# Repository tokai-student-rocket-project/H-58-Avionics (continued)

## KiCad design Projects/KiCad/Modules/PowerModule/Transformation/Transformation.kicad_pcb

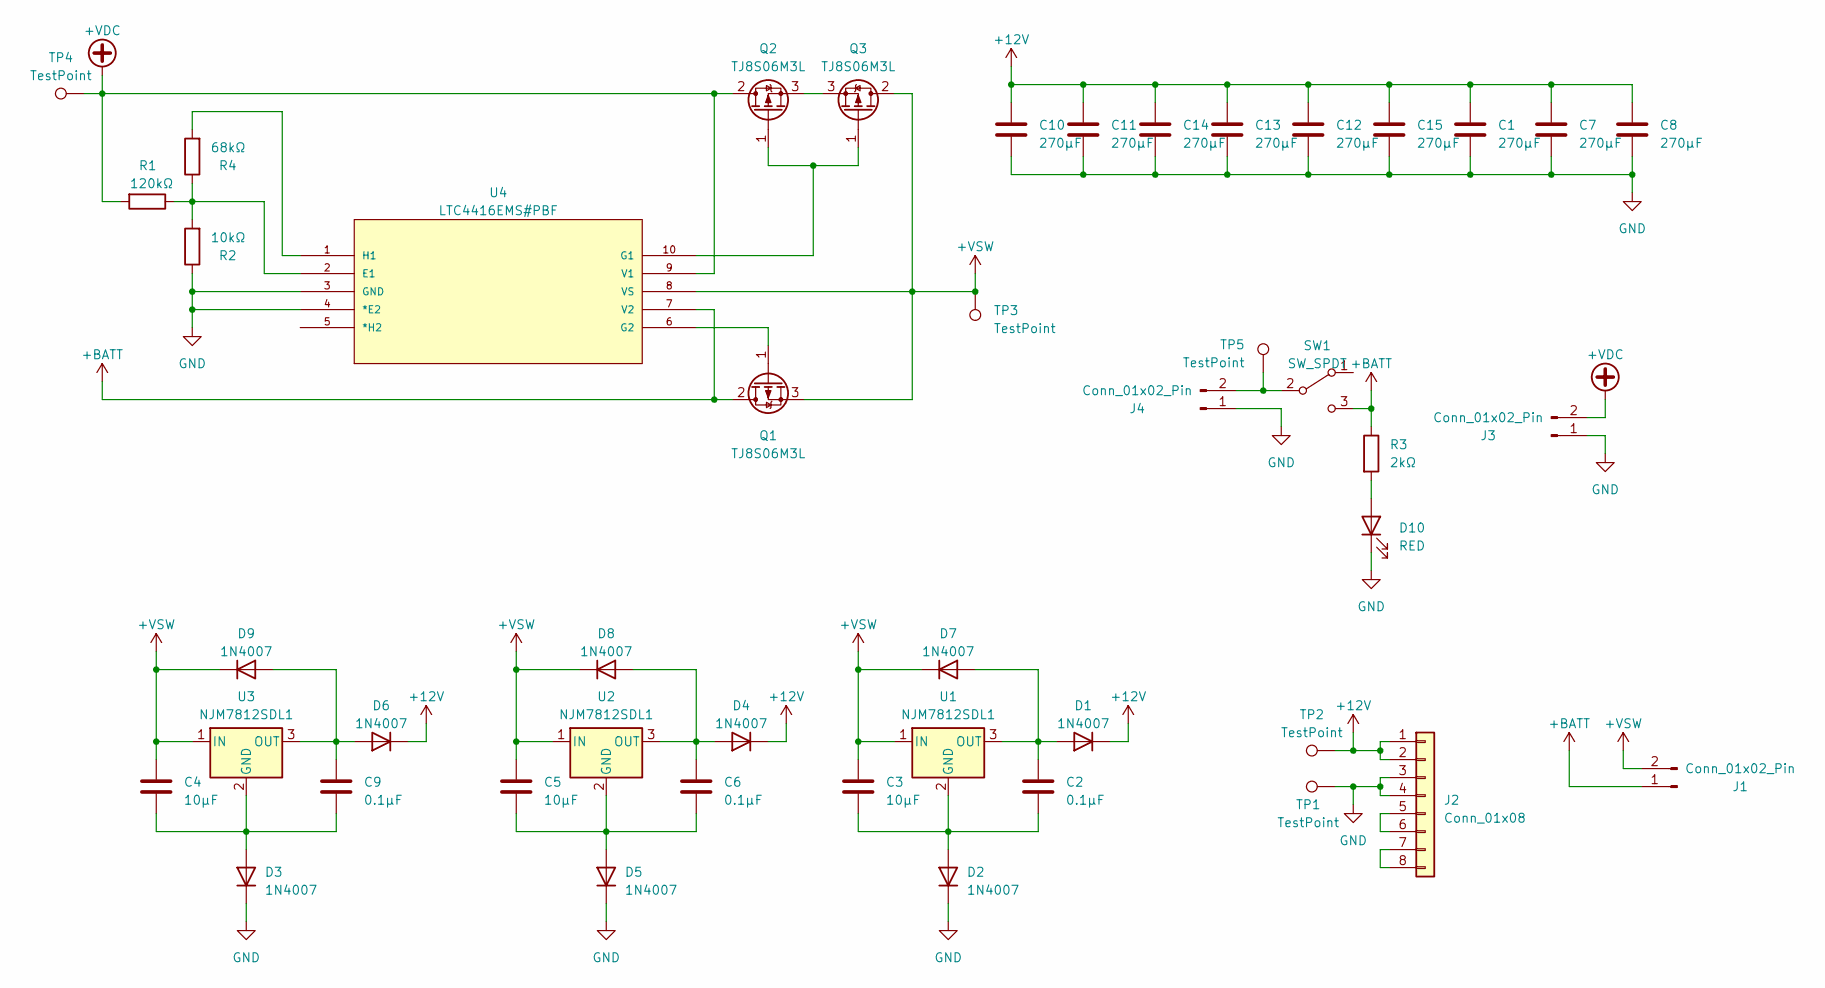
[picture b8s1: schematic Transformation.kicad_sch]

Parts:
C1, C7, C8, C10, C11, C12, C13, C14, C15: 270μF; CP_Radial_D10.0mm_P3.50mm
C2, C6, C9: 0.1μF; C_0603_1608Metric_Pad1.08x0.95mm_HandSolder
C3, C4, C5: 10μF; C_0603_1608Metric_Pad1.08x0.95mm_HandSolder
D1, D2, D3, D4, D5, D6, D7, D8, D9: 1N4007; D_SOD-123F
D10: RED; LED_0603_1608Metric_Pad1.05x0.95mm_HandSolder
J1, J3, J4: Conn_01x02_Pin; Hirose_DF1B
J2: Conn_01x08; Hirose_DF11B-8DP-2DS
Q1, Q2, Q3: TJ8S06M3L; TO-252-2
R1: 120kΩ; R_0805_2012Metric_Pad1.20x1.40mm_HandSolder
R2: 10kΩ; R_0805_2012Metric_Pad1.20x1.40mm_HandSolder
R3: 2kΩ; R_0603_1608Metric_Pad0.98x0.95mm_HandSolder
R4: 68kΩ; R_0603_1608Metric_Pad0.98x0.95mm_HandSolder
SW1: SW_SPDT; 2MS1T1B4M7QES
TP1, TP2, TP3, TP4, TP5: TestPoint; Pin_D1.0mm_L10.0mm
U1, U2, U3: NJM7812SDL1; TO-252-2
U4: LTC4416EMS#PBF; MSOP-10-1EP_3x3mm_P0.5mm_EP1.73x1.98mm; MANUFACTURER_PART_NUMBER ltc4416ims1

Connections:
+12V: C1.1, C7.1, C8.1, C10.1, C11.1, C12.1, C13.1, C14.1, C15.1, D1.1 (K), D4.1 (K), D6.1 (K), J2.1, J2.2, TP2.1
+BATT: J1.1, Q1.2 (D), R3.1, SW1.3 (C), U4.7 (V2)
+VDC: J3.2, Q2.2 (D), R1.2, TP4.1, U4.9 (V1)
+VSW: C3.1, C4.1, C5.1, D7.1 (K), D8.1 (K), D9.1 (K), J1.2, Q1.3 (S), Q3.2 (D), TP3.1, U1.1 (IN), U2.1 (IN), U3.1 (IN), U4.8 (VS)
GND: C1.2, C7.2, C8.2, C10.2, C11.2, C12.2, C13.2, C14.2, C15.2, D2.1 (K), D3.1 (K), D5.1 (K), D10.1 (K), J2.3, J2.4, J3.1, J4.1, R2.1, TP1.1, U4.3 (GND), U4.4 (*E2)
unnamed: C2.1, D1.2 (A), D7.2 (A), U1.3 (OUT)
unnamed: C2.2, C3.2, D2.2 (A), U1.2 (GND)
unnamed: C4.2, C9.2, D3.2 (A), U3.2 (GND)
unnamed: C6.1, D4.2 (A), D8.2 (A), U2.3 (OUT)
unnamed: C5.2, C6.2, D5.2 (A), U2.2 (GND)
unnamed: C9.1, D6.2 (A), D9.2 (A), U3.3 (OUT)
unnamed: D10.2 (A), R3.2
unnamed: J2.5, J2.6
unnamed: J2.7, J2.8
unnamed: J4.2, SW1.2 (B), TP5.1
unnamed: Q1.1 (G), U4.6 (G2)
unnamed: Q2.1 (G), Q3.1 (G), U4.10 (G1)
unnamed: Q2.3 (S), Q3.3 (S)
unnamed: R1.1, R2.2, R4.1, U4.2 (E1)
unnamed: R4.2, U4.1 (H1)

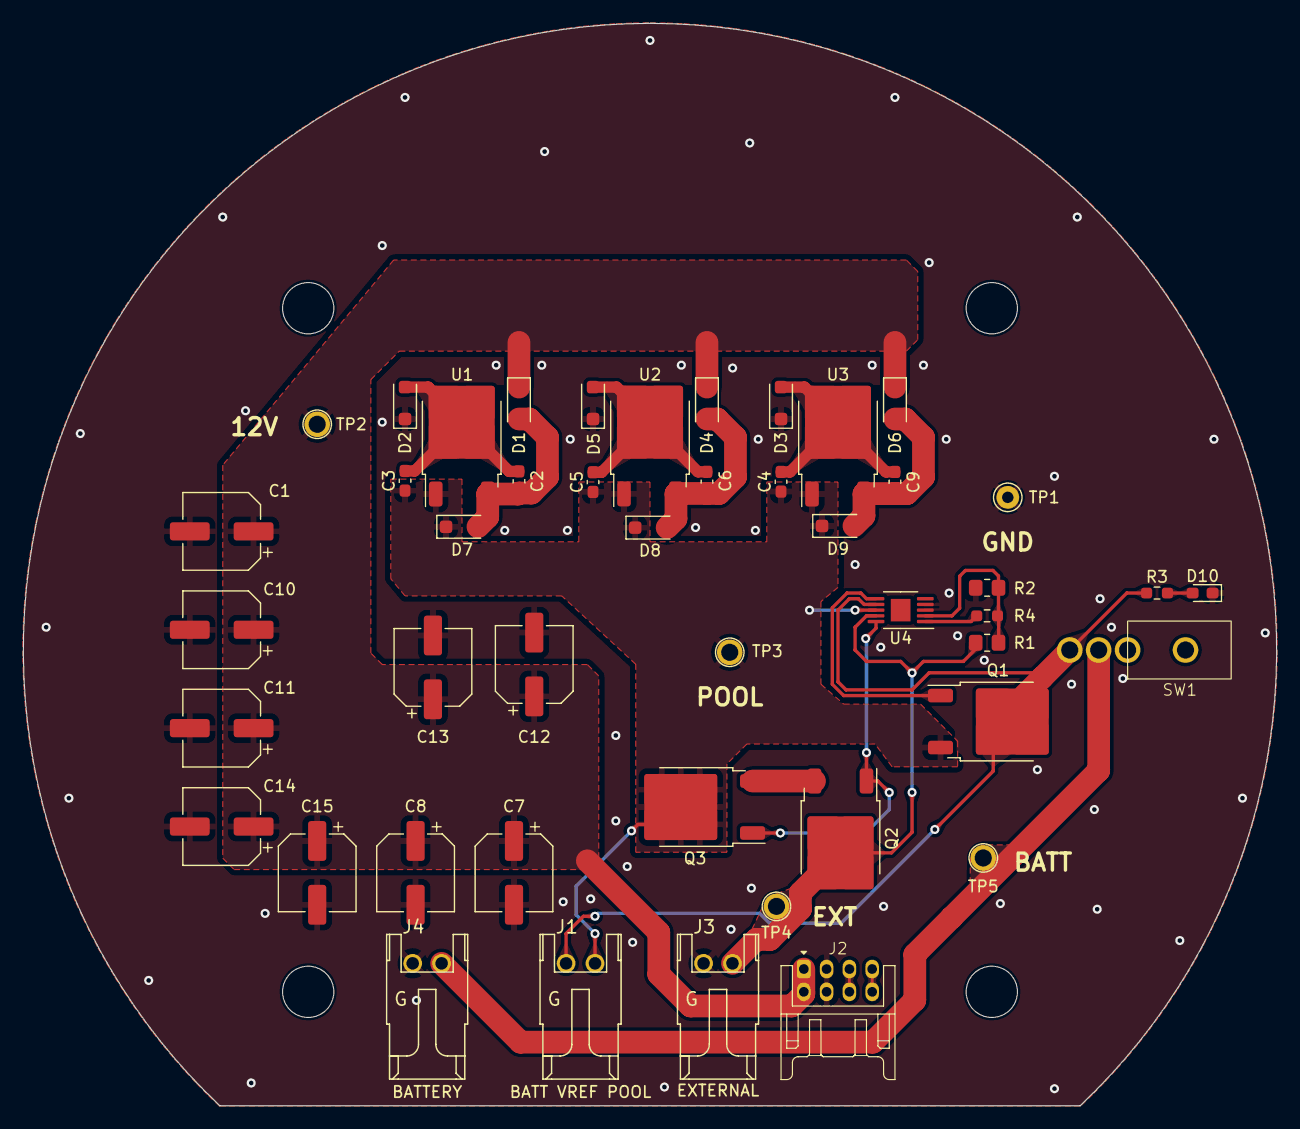
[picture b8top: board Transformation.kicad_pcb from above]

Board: 2 copper layers, 110.0 x 95.0 mm, 46 parts (0 on the bottom side), 20 nets.

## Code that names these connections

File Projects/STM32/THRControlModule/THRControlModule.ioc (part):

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Mcu.Name=STM32F303K(6-8)Tx
Mcu.Package=LQFP32
Mcu.UserName=STM32F303K8Tx
PA10.Mode=Synchronous
PA10.Signal=USART1_RX
PA11.Mode=CAN_Activate
PA11.Signal=CAN_RX
PA12.Mode=CAN_Activate
PA12.Signal=CAN_TX
PA5.Mode=Full_Duplex_Master
PA5.Signal=SPI1_SCK
PA6.Mode=Full_Duplex_Master
PA6.Signal=SPI1_MISO
PA7.Mode=Full_Duplex_Master
PA7.Signal=SPI1_MOSI
PA8.Mode=Synchronous
PA8.Signal=USART1_CK
PA9.Mode=Synchronous
PA9.Signal=USART1_TX
PB0.GPIOParameters=PinState,GPIO_Label
PB0.GPIO_Label=Thermocouple_CS
PB0.PinState=GPIO_PIN_SET
PB0.Signal=GPIO_Output
PF0\ /\ OSC_IN.Mode=HSE-External-Oscillator
PF0\ /\ OSC_IN.Signal=RCC_OSC_IN
PF1\ /\ OSC_OUT.Mode=HSE-External-Oscillator
PF1\ /\ OSC_OUT.Signal=RCC_OSC_OUT
RCC.HSEPLLFreq_Value=8000000
RCC.HSE_VALUE=8000000
RCC.SYSCLKFreq_VALUE=8000000
board=custom

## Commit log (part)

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2023-06-20 Kicadの更新
2023-06-20 CDRおわ
2023-06-20 チャタリング対策を追加
2023-06-21 計測モジュールにCANのラッパライブラリを追加（includeに相対パス指定できないの悲しい）
2023-06-21 フライトモジュールにCANのラッパライブラリを追加
2023-06-21 Arduino向けのCANのラッパライブラリを追加
2023-06-21 ピン初期化周りを変更、100Hzでタスクを回すように変更
2023-06-21 CANの抽象度を上げた
2023-06-21 GSEからバルブ開 バルブ閉を受け取ることができた。
2023-06-21 名前空間を整理
2023-06-21 起動モードがデバッグの時は電圧監視をしないように変更（ピンが競合するため）
2023-06-21 各部名称を変更
2023-06-21 変更後のpngを追加
2023-06-21 不知火の抽象化ライブラリを追加
2023-06-21 SDが不正の時のLED点滅をいい感じのライブラリに移植
2023-06-22 ガーバーを再出力
2023-06-22 バルブ制御モジュールを追加
2023-06-22 基板を更新（最終確認中）
2023-06-22 温度補正を追加中
2023-06-22 リフトオフ検知とリセット検知に連続検知を追加
2023-06-23 BMEのログをとった
2023-06-23 周波数解析を追加
2023-06-23 CANのIdを整理
2023-06-23 CANでやり取りするデータを整理
2023-06-23 フライトモードの遷移と遷移後の動作を統合
2023-06-24 pluginを追加
2023-06-24 ValveControlModuleのガーバーデータを追加
2023-06-24 AdafruitのMAX31855ライブラリーに変更
2023-06-24 Adafruitのライブラリ仕様に変更
2023-06-26 イベントの出力を追加
2023-06-26 CANのイベントのパケット構成を変更
2023-06-26 すべてのモジュールがSETUPイベントを出力するように変更
2023-06-26 unionからmemcpyを使った実装に変更
2023-06-26 CANMCPに送信用の関数を追加
2023-06-26 🚧 ブランチを追加
2023-06-26 🍻 エクセルをゴニョゴニョ変更
2023-06-26 ✨ 強制分離を追加
2023-06-26 🐛 memcpyのポインタを、ミスっていたので修正
2023-06-27 🎨 離昇してからの経過時間を返すflightTime()関数を追加
2023-06-27 EMA計算用のクラスを追加
2023-06-27 頂点検知(!=頂点予測)用のクラスを追加
2023-06-27 ✨ 分離保護を実装
2023-06-27 🎨 無駄にスネークケースだったことろをキャメルケースに修正
2023-06-27 🎨 受信側を更新
2023-06-28 🚚 通信モジュールの受信側のパスを変更
2023-06-28 ✨ ミッションモジュールの受信を追加
2023-06-28 🐛 計測モジュールの気温送信を消していたので追加
2023-06-28 ⚡️ CANの安定化のためにボーレートを80kbpsに変更
2023-06-28 CANのボーレートとTransmitPriorityを変更
2023-06-28 🎨 状態検知を10Hzに変更
2023-06-28 ✨ イベントのダウンリンクを実装
2023-06-28 🎨 フライトピンの状態検知は100Hzに戻した
2023-06-28 🎨 CANのボーレートを変更
2023-06-28 CAN受信LEDの点滅タイミングを欲しいパケットを受信した時のみに修正
2023-07-01 夢の国の音楽を追加
2023-07-01 短音1回, 2回, 長音1回をノンブロックングで追加
2023-07-01 CANのイベントパケットからペイロードデータを削除
2023-07-01 CAN-BUSのリストを更新
2023-07-01 CANのコマンドパケットにはパスワードいらなかったので削除
2023-07-01 参照気圧設定コマンドを追加
2023-07-01 ⚡️ 温度計測の方法を変更
2023-07-03 🚧 ⚡️ ブザータイミングの作業中/ブザーの機能を追加、確認用LEDの追加
2023-07-03 ✨ シャットダウン時に例の曲を流すように変更
2023-07-03 コードをコメントに追加
2023-07-03 🔥 余計なコメントを削除
2023-07-03 💬 コマンド部分のCANリストを変更
2023-07-03 🎨 参照気圧セットコマンドを分割
2023-07-03 🐛 CAN受信処理のラベルを修正
2023-07-03 システムデータ通信モジュールの受信側から計測モジュールへのアップリンクを追加
2023-07-03 ⚡️ 各モード遷移時にブザー音を追加
2023-07-03 ♻️ CANのbpsを変更
2023-07-03 ✏️ 指摘されたので直しました。文句ありますか？
2023-07-03 ✨ 参照気圧を設定できた時にイベントをダウンリンクするように変更
2023-07-03 💬 READMEの参照気圧設定コマンドのデータ長をミスっていたので修正
2023-07-03 💬 READMEのCANリストにエラー追加
2023-07-03 🎉 バルブ制御モジュールにTHR制御モジュール（存在しない）のコードを移植
2023-07-04 🎉 バルブ制御モジュールのコードを追加
2023-07-04 テスト用に製作したフォルダ達を削除
2023-07-04 ✨ キー照合の失敗時のエラーダウンリンクを実装
2023-07-04 伝送試験用に受信側のログ出力を編集
2023-07-04 🎨 ADXLをSPIに変更（通信は未実装）
2023-07-04 ✨ サーボモーターのRAMにアクセスできるようになり、各種パラメータを取得可能に。
2023-07-05 🚧 ADXLの初期化処理をSPIに変更
2023-07-05 🔊 受信側のログ出力をcsvに変更
2023-07-05 ♻️ 余計な個所を微修正
2023-07-05 ログ置き場を作成
2023-07-05 エアーデータコミュニケーションツールを追加
2023-07-05 システムデータコミュニケーションモジュールを追加しました。
2023-07-05 エアーデータコミュニケーションモジュールを追加
2023-07-05 システムモードコミュニケーションモジュールの解析を追加しました。
2023-07-05 練習しました
2023-07-05 ADXLのデータ出力をSPIに変更（出力されない）
2023-07-05 ⏪ 受信側のログをJsonに戻した
2023-07-05 解析のエクセルを追加
2023-07-05 表を整形
2023-07-06 📝 ロングラン試験のREADMEを追加
2023-07-06 ✨ ロングラン用に必要なログをダウンリンクするコードを追加
2023-07-06 ♻️ コードにコメントを追加
2023-07-06 💬 試験の概要的なものをREADMEに記載
2023-07-06 🔊 1回目のロングラン試験のログを追加
2023-07-06 🔊 ログのファイル名を変更
2023-07-06 🔊 2回目のロングラン試験のログを追加
2023-07-06 🔊 速報用の解析を追加
2023-07-06 🔊 ミッションモジュールのログを追加
2023-07-06 🙈 エクセルの一時ファイルをgitignoreに追加
2023-07-06 📝 ミッションモジュールの解析を追加
2023-07-06 🔊 ログを移動
2023-07-06 🔊 1回目のログを整形
2023-07-06 🚚 ログのファイル名を変更
2023-07-06 🔊 2回目のログを整形
2023-07-06 🔊 解析を追加
2023-07-07 ✨ climbIndexの算出を計測モジュールで行うように変更
2023-07-07 ✨ フライトモードの頂点検知を計測モジュールが算出した落下検知を使用したものに変更
2023-07-07 🎨 高度算出をTrajectoryライブラリに移植
2023-07-07 ⚡️ Trajectoryライブラリのupdate()ですでに用意した高度を使用できるように変更
2023-07-07 ⚡️ 読み出すことのできるデータのみ実装
2023-07-07 ✨ CANで送るデータの追加
2023-07-07 ⚡️ CANの動作が行えているかのチェックする機能を追加．言語よわよわなのでコメントアウトで実装
2023-07-07 🎨 読み出す値のコメントを追加．
2023-07-07 頂点検知試験用のコードを追加
2023-07-08 レジスタの書き込みをwrite()関数に切り出し
2023-07-08 🧐 Adafruitライブラリでは動作することを確認
2023-07-08 ADXLの自作ライブラリでの動作を確認
2023-07-08 🎨 ODRを3200Hzに変更, 出力値の単位をm/s2に変更
2023-07-08 ♻️ SPI関係の関数を整理
2023-07-08 ✨ FRAMの読み書きを実装
2023-07-08 ⚗️ FRAMの容量把握ようの実験コードを追加
2023-07-08 ✨ 簡易的なFRAMへのログ保存を実装
2023-07-08 ✨ フライトモードがSTANDBYとLANDの間のみログを保存するように変更
2023-07-08 🐛 ログ保存OFFの状態で起動するように修正
2023-07-08 ♻️ CAN受信処理を関数に摘出
2023-07-08 ♻️ RecorderからLoggerに名称変更
2023-07-08 💡 inoに一通りコメントを追加
2023-07-08 ♻️ 充填確認との区別のためにTemperatureをOutsideTemperatureに名所変更
2023-07-08 inoの変数に単位を追加
2023-07-08 💡 BMEにコメントを追加
2023-07-08 🚧 コメントを書くコードにTODOを追加
2023-07-10 💡 BNO055にコメントを追加
2023-07-10 計測モジュール関係に一通りコメントを追加
2023-07-10 ♻️ CANの関数receiveStatus()をreceiveSystemStatus()に名称変更
2023-07-10 ♻️ CANの関数からCommandを削除して名称変更
2023-07-10 ♻️ sendVector()をsendVector3Dに名称変更
2023-07-10 ♻️ sendSystemStatus()の引数名をxxStateに変更
2023-07-10 🚧 バッテリー切れ(死)
2023-07-10 Revert "🚧 バッテリー切れ(死)"
    This reverts commit 6ca955eedc5a3f155d30bc1fa7058b48da335df3.
2023-07-10 🔊 H-49とH-57のログを追加
2023-07-10 高度50m以上でないと落下判定しないように変更
2023-07-10 ✏️ 変数名の誤字を修正
2023-07-10 ⚡️ 重そうなSDの認識処理を1Hzタスクに変更
2023-07-10 ⚡️ SDの初期検知を廃止
2023-07-10 🚧 BMEとBNOをコメントアウト
2023-07-10 ⚡️ BNO055ライブラリを最低限の実装で自作
2023-07-10 ⏪ BME280はそのままで
2023-07-10 🎨 LoggerにSdを統合
2023-07-10 ⚡️ SD検知不可時の処理をシンプルに変更
2023-07-10 🔥 不要なコードを削除
2023-07-10 ✨ SDのログ開始を追加
2023-07-10 ✨ ログ保存開始時csvにヘッダーを書き込むように変更」
2023-07-10 ✨ SDへのデータ書き込みを実装(1668Bオーバー)
2023-07-10 ログファイルはMessagePackで保存するようにした
2023-07-10 🎨 SDカードにバイナリで書き込むように変更
2023-07-10 ✨ 毎回新しいファイルを作るように変更
2023-07-10 ✨ SD不正時にエラーを発行するように変更
2023-07-10 ✨ 参照気圧を5秒間隔で送信する機能を追加
2023-07-10 ✨ センサのキャリブレーション状態を送信する機能を追加
2023-07-11 分離制御のロジック図を更新
2023-07-11 頂点検知試験用のモックデータを20Hzに修正
2023-07-11 ✨ SCMでSD不正のエラーを受け取る処理を追加
2023-07-11 ✨ SCMの受信側を実装
2023-07-11 ✨ FRAM動確
2023-07-11 🎨 DoLoggingをCANで送るように変更
2023-07-11 ✨ フライトモジュールにFRAMへのデータ保存を実装
2023-07-12 🐛 FRAMをクリアする前に書き込み位置をリセットするように修正
2023-07-12 🐛 FRAMの容量を超えていてもSDへは書き込むように修正
2023-07-12 🐛 FRAMのクリアの前にライトイネーブルが設定されていなかった問題を修正
2023-07-12 ✨ フライトモジュールのFRAMへのログ保存を実装
2023-07-12 🎨 ログ保存の開始と終了を関数に切り出し
2023-07-12 ✨ 想定着地時間の3秒前にカメラオフにする
2023-07-12 🍻 燃焼中は1kHz計測を行い、後からダウンリンク送信する処理を簡易的に実装
2023-07-12 ♻️ フライトモード変更を関数に切り出し
2023-07-12 💡 コメントを追加
2023-07-12 💡 AnalogVoltageにコメントを追加
2023-07-12 💡 Buzzerにコメントを追加
2023-07-12 🐛 ブザーをトグルする前にOFFにするように修正(一生なり続ける問題解消)
2023-07-12 🎨 ログ保存の状態をLoggerクラス内で保存するように変更
2023-07-12 ✨ フライトモード管理用のライブラリを実装
2023-07-13 ✨ フライトモードを認識する関数を実装
2023-07-13 ✨ フライトモードの初期値をインスタンス化時点でSLEEPにするように変更
2023-07-13 🎨 フライトモードを列挙型の状態で渡すように変更
2023-07-13 💥 列挙型を摘出
2023-07-13 logicを追加
2023-07-13 ✨ CAN通信部を実装
2023-07-13 🎨 OutputPinとPullupPinをもう一段階ラップするクラスを実装
2023-07-13 🐛 SDが不正でもログ開始はするように修正
2023-07-13 SwitchのOPENとCLOSEが逆だったので修正
2023-07-13 ⚡️ パフォーマンス改善のためログ保存開始時にSDが認識できない時は初期化しないように修正
2023-07-13 ⚰️ 不要なインクルードを削除
2023-07-13 🎨 名前空間を整理
2023-07-13 ♻️ 起動モードのスイッチを整理
2023-07-13 🎨 フライトモード遷移時処理の実行手順を変更
2023-07-13 🔀 競合を解消
2023-07-13 🐛 Varを使った実装に修正
2023-07-13 🎨 デバッグ用のコードをコメントアウト
2023-07-13 🐛 CAN受信を修正
2023-07-13 🎨 時間を管理するクラスを実装
2023-07-13 🚧 LoRa管理用のクラスを追加
2023-07-13 🎨 エアデータ通信モジュールでTransmitterを利用するように変更
2023-07-14 ♻️ 不要なコメントアウトを削除
2023-07-14 ✨ バルブ制御モジュールからのCAN受信とダウンリンクを追加
2023-07-14 ✨ Transmitterを簡易的に実装
2023-07-14 ✨ フライトモードオンコマンドを実装
2023-07-14 🔥 Transmitterにメリットを感じなかったので廃止
2023-07-14 ⚡️ CANで送るデータサイズを縮小
2023-07-14 ✨ 現在のモードを10HzでCANに流す機能を追加
2023-07-14 🐛 Taskの名前変更し間違えたので変更
2023-07-14 🚧 エラー送信がうまく動作しているのか確認．
2023-07-14 ✨ バルブ制御モジュールのLAUNCH信号状態検知でフライトモードを開始を実装
2023-07-14 🚧 PC移動コミット
2023-07-15 🔥 バルブ制御モードの連続検知を廃止
2023-07-17 💡 自作ライブラリたちにコメントを追加
2023-07-17 💡 通信モジュールにコメントを追加
2023-07-19 ⚡️ CAN送信レートを変更
2023-07-19 ⚡️ 送信レートを素数に変更
2023-07-19 ⚡️ 燃焼実験時のコンフィグを確定
2023-07-20 フライトピンの接触不良でした
2023-07-22 🐛 ダウンリンクを調整
2023-07-22 🐛 姿勢角と偽って地磁気を送信していた問題を修正
2023-07-25 📝 手順書用の写真を追加
2023-07-25 ✨ 上昇率の算出を実装
2023-07-25 ⚡️ エアデータを平滑化するように変更
2023-07-25 電圧3種類を1つのパケットに圧縮
2023-07-25 🐛 電圧をCAN送信の引数が間違っていたので修正
2023-07-26 飛翔時間のダウンリンクを追加
2023-07-26 🏷️ ステータスをダウンリンクするときの型をuint8_tからboolに変更
2023-07-26 ⚡️ コマンドの受信成功率を改善
2023-07-26 🐛 座標軸を修正
2023-07-28 広報に関する情報を追加
2023-07-28 ペーパークラフトを追加
2023-07-28 noteとasideの試し
2023-07-28 noteとasideは使えなかった
2023-07-28 note infoも無理
2023-07-29 ✨ 計測モジュールにダンパーを追加
2023-07-29 ✨ ダンパーを追加
2023-07-29 ⚡️ mcu温度とmotor温度を温度系としてまとめた（はず...） 大学行く前コミット
2023-07-29 LEDをオフ
2023-07-29 ⚡️ motor温度，mcu温度，電流，電圧を１つにまとめた
2023-07-29 3023948a56a2dfa1adf925e6bd497c5dc962d727 これに対応
2023-07-29 LoRaの送信キューを実装
2023-07-29 ⚡️ モーターに関するデータを1つに集約してCANへ送る機能の追加
2023-07-29 ✨ バルブ角度の受信を追加
2023-07-30 くぁｓｗでｆｒｔｇｙふじこｌｐ
2023-07-30 🔥 処理をまとめたので余計な処理を削除
2023-07-30 🔥 ValveControlModuleに主な機能を譲渡
2023-07-30 資料を整理
2023-07-30 組み立て手順書を追加
2023-07-31 🔥 関数をまとめた．
2023-07-31 ダウンリンクのパケットにmillisを追加
2023-07-31 🎨 LEDON
2023-07-31 姿勢角を修正
2023-07-31 ✨ サーボモーターからのステータス情報を受け取りCAN-BUSへ情報を流す機能の追加．
2023-07-31 充填確認温度を受信できるように変更
2023-07-31 ✨ リセットコマンドを実装
2023-07-31 🐛 CANSTMのヘッダーをコピー
2023-08-01 🐛 スタンバイモードの時にリセットするとスリープに、それ以降にリセットするとシャットダウン
2023-08-01 ⚡️ 微分上手く行ったよ
2023-08-01 ✨ ⚡️ モーターステータス情報を追加/バルブ開の角度を-55度に変更
2023-08-02 タイマーをH-58に変更
2023-08-02 🐛 SN4のピンをSN3として使うことで、分離中ログが保存されていなかった問題を修正
2023-08-02 菊水，PMM18-2.5DUのマニュアルを追加
2023-08-02 ODEKEKE_Listを更新
2023-08-02 コネクタを追加
2023-08-03 📝 地上局それぞれのレシーバーの名称を変更
2023-08-03 FRAMのデータシートを追加
2023-08-03 受信機のJSONを短縮
2023-08-03 📝 くそでかワッシャーについてのドキュメントを追加
2023-08-04 🐛 不正なデータを弾けるように修正
2023-08-04 FRAM使用率のダウンリンクを追加
2023-08-04 ✨ GNSS関連でダウンリンクデータを追加
2023-08-04 📝 RENYシリーズを各種10個ほどに仮決定
2023-08-04 📝 コネクタBOXの個数を更新
2023-08-04 🚑 長時間放置した場合FRAMの書き込み位置がリセットされる問題を修正
2023-08-04 📝 コネクタ周りの個数を更新
2023-08-04 📝 バスパワーラインなどBOXを追加
2023-08-04 📝 ダイオードBOXを更新
2023-08-04 📝 コネクタBOXを更新
2023-08-05 🐛 ADXLの出力を修正
2023-08-05 ✨ 燃焼時と分離時のタスクを追加
2023-08-05 ✨ ミッションモジュールのメモリ使用率ダウンリンクを追加
2023-08-05 ⚡️ 点火前から計測できるように変更
2023-08-05 遅延送信を実装
2023-08-05 ⚡️ 計測と送信のタイミングを調整
2023-08-05 🚚 タスク名を変更
2023-08-05 ✨ 遅延送信を仮で実装
2023-08-05 ✨ クオータニオン計測を追加
2023-08-06 lsbを修正
2023-08-06 ✨ 送信処理を実装
2023-08-06 🎨 ミッションステータスのダウンリンクをSCMからMMへ移動
2023-08-06 ✨ ミッションステータスを追加
2023-08-07 📝 部品表(csv)の追加
2023-08-07 📝 ValveControlModuleくんの画像を追加
2023-08-07 📝 READMEの更新
2023-08-07 📝 READMEの見出しを修正
2023-08-07 📝 SoftwareDocumentの追加
2023-08-08 ソースコードとKiCadをcomponentsの中に移動
2023-08-08 📝 電源系もcomponentsの中に移動
2023-08-09 RasPsdの故障時に必要なものを追記
2023-08-09 計測モジュールのREADMEを記載
2023-08-09 工具箱を編集
2023-08-09 熱収縮を工具箱に移動
2023-08-10 CANSTMライブラリをバルブ情報に対応
2023-08-10 バルブ情報の受信を追加
2023-08-10 熱電対温度3種類のログ保存を追加
2023-08-10 ログダンパーを熱電対温度に対応
2023-08-10 バルブ情報のログ保存を追加
2023-08-10 ログダンパーをバルブ情報に対応
2023-08-11 ダウンリンクする温度をCOLD_JUNCTIONからCOLLECTEDに変更
2023-08-12 分離コンフィグの時間をH-58仕様に変更
2023-08-12 分離保護高度をX+1.6secでの高度32mに変更
2023-08-12 チューブ中温度計測を追加
2023-08-15 解析で計算できるものは保存しないように変更
2023-08-15 🚧 一度コミット
2023-08-15 機体間通信モジュール性能情報の受信を実装
2023-08-15 STMライブラリをこぽー
2023-08-16 ブザーを一旦オフ
2023-08-16 ✨ millis()を用いタスクのHzをCANに送信する機能の追加
2023-08-16 ブザーが動作時に鳴らないよう設定
2023-08-16 🚧 ブザーを打上げ前に動作させること!!!!
2023-08-16 無線周波数を変更
2023-08-17 ミッションモジュールのログ抽出を追加
2023-08-17 うごかじゃい
2023-08-17 分離コンフィグを更新
2023-08-17 FRAMを使えない問題を修正
2023-08-17 1kHzのログmicrosじゃないとわからんわ
2023-08-18 ADXLの生値を保存するように変更
2023-08-18 受信機とログダンパーを生値に対応
2023-08-18 パケットサイズを32Bから24Bに変更
2023-08-18 いらんもんを削除
2023-08-18 ブザーを有効化
2023-08-18 分離保護高度を更新
2023-08-18 ADXLを修正
2023-08-18 温度の受信を修正
2023-08-18 新しいサーミスタ用に校正
2023-08-18 🔖 バージョン1.0.0をリリース
2023-08-19 バルブ制御モジュールのブザーを有効か
2023-08-20 フライトピン開放状態で起動した場合はフライトモードを進めないように変更
2023-09-04 📝 渡航に渡航反省会のリンクを挿入
2023-09-20 詳細報告書用のフォルダを追加
2023-09-20 カラーパレットを追加
2023-09-20 ✨ UART通信のテンプレートを追加
2023-09-20 ✨ RS485のテンプレートを追加
2023-09-20 ✨色が被っていたのでRS485の色を変更
2023-09-20 🚧 アクチュエーター周りを作成
2023-09-20 🚧 ValveSystem7割程完成
2023-09-20 🚧 ValveSystemの写真を追加
2023-09-23 電源系の図を追加
2023-09-23 通信系のブロック図を追加
2023-09-23 ⚡️ ブロックダイアグラムを作成
2023-09-23 表用のエクセルを追加
2023-09-23 センサ系のブロック図を追加
2023-09-24 3dモデルを修正
2023-09-24 詳細報告書ないの画像を追加
2023-09-24 アンビリカルケーブルの説明用写真を追加
2023-09-24 説明用の写真を追加
2023-09-24 説明用の画像を追加
2023-09-24 名前を変更
2023-09-24 搭載計器全体の写真を追加
2023-09-24 修正したバルブシステムのブロック図を追加
2023-09-24 アンビリカルケーブルの説明用画像を追加
2023-09-24 図とか表とか追加
2023-09-28 不知火4ソフトポートを追加
2023-10-12 READMEを簡単にまとめた
2023-10-12 Create LICENSE
2023-11-13 キャッシュを削除
